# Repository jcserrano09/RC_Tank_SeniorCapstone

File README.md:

brd, sch, and f3z files are in Submission for Manufacture folder

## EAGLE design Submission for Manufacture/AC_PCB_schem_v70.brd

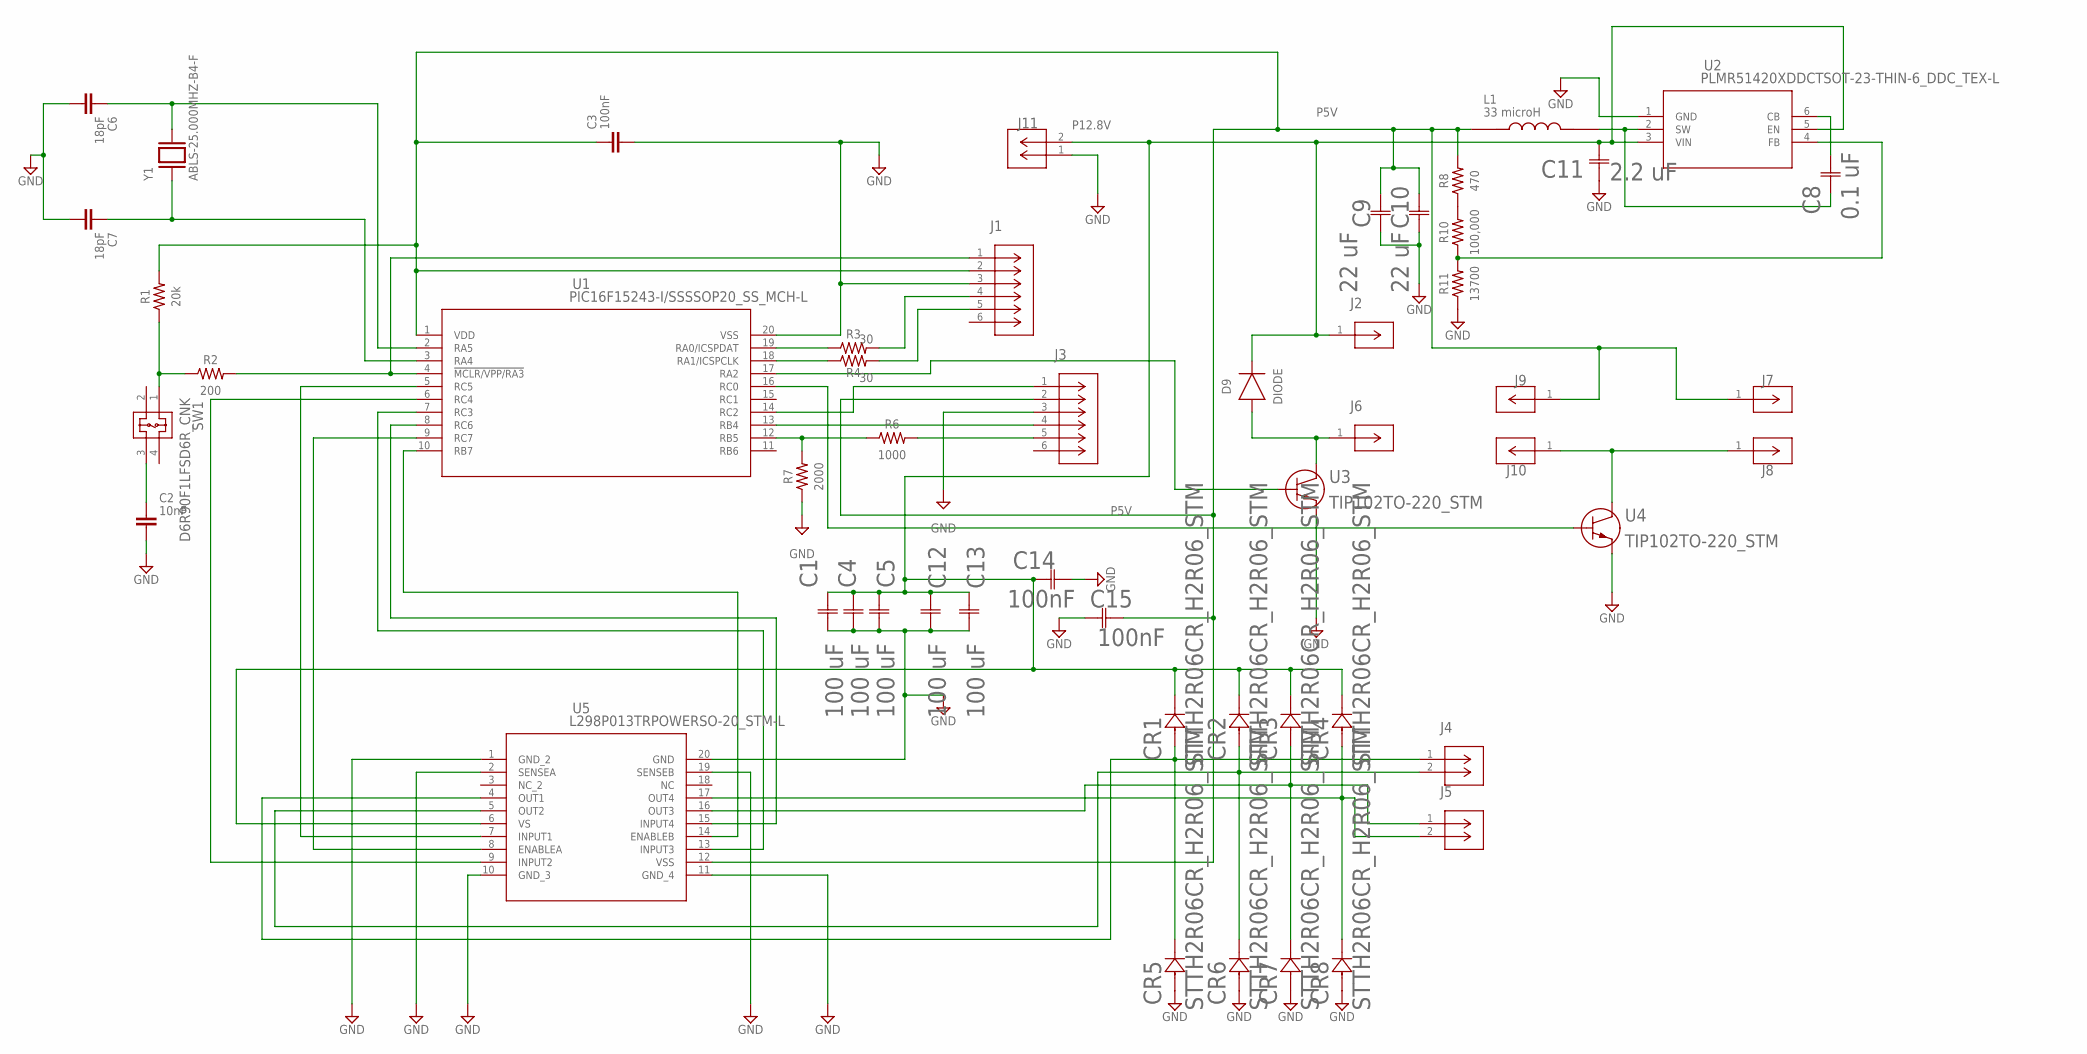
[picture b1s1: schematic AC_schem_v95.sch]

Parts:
C1, C4, C5, C12, C13: 100 uF; CAP_CL31_SAM-L
C2: 10nF; CAPC2012X110
C3: 100nF; CAPC2012X110
C6, C7: 18pF; CAPC2012X110
C8: 0.1 uF; CAP_CL21_SAM-L
C9, C10: 22 uF; CAP_CL21_SAM-L
C11: 2.2 uF; CAP_CL21_SAM-L
C14, C15: 100nF; CAP_CL05_SAM-L
CR1, CR2, CR3, CR4, CR5, CR6, CR7, CR8: STTH2R06CR_H2R06_STM; CR_H2R06_STM
D9: DIODE; DIOM7959X625N
J1: PH1RB-06-UACONN_PH1RB-06; CONN_PH1RB-06
J2, J6, J7, J8, J9, J10: SMC-1-01-1-GTCONN_SMC-1-01-1-GT_ADM; CONN_SMC-1-01-1-GT_ADM
J3: PPTC061LFBN-RCCONN6_061LFBN-RC_SUL; CONN6_061LFBN-RC_SUL
J4, J5, J11: PPTC021LFBN-RCCONN2_LFBN-RC_SUL; CONN2_LFBN-RC_SUL
L1: 33 microH; INDAD1430W80L950D400
R1: 20k; RESC2012X65
R2: 200; RESC2012X65
R3, R4: 30; RESC2012X65
R6: 1000; RESC2012X65
R7: 2000; RESC2012X65
R8: 470; RESC2012X65
R10: 100,000; RESC2012X65
R11: 13700; RESC2012X65
SW1: D6R90F1LFSD6R_CNK; D6R_CNK
U1: PIC16F15243-I/SSSSOP20_SS_MCH-L; SSOP20_SS_MCH-L
U2: PLMR51420XDDCTSOT-23-THIN-6_DDC_TEX-L; SOT-23-THIN-6_DDC_TEX-L
U3, U4: TIP102TO-220_STM; TO-220_STM
U5: L298P013TRPOWERSO-20_STM-L; POWERSO-20_STM-L
Y1: ABLS-25.000MHZ-B4-F; XTAL_ABLS-25.000MHZ-B4-F

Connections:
GND: C1.2, C2.2, C3.2, C4.2, C5.2, C6.2, C7.2, C9.2, C10.2, C11.2, C12.2, C13.2, C14.2, C15.1, CR5.2 (K), CR6.2 (K), CR7.2 (K), CR8.2 (K), J1.3, J3.3, J11.1, R7.1, R11.1, U1.20 (VSS), U2.1 (GND), U3.3 (E), U4.3 (E), U5.1 (GND_2), U5.2 (SENSEA), U5.10 (GND_3), U5.11 (GND_4), U5.19 (SENSEB), U5.20 (GND)
unnamed: J3.5, R6.2
unnamed: J3.4, U1.13 (RB4)
unnamed: J3.1, U1.14 (RC2)
unnamed: U1.5 (RC5), U5.7 (INPUT1)
unnamed: U1.6 (RC4), U5.9 (INPUT2)
unnamed: U1.9 (RC7), U5.8 (ENABLEA)
unnamed: U1.7 (RC3), U5.13 (INPUT3)
unnamed: U1.10 (RB7), U5.14 (ENABLEB)
unnamed: CR2.2 (K), CR6.1 (A), J4.2, U5.5 (OUT2)
unnamed: U1.17 (RA2), U3.1 (B)
unnamed: C2.1, SW1.3
unnamed: CR1.2 (K), CR5.1 (A), J4.1, U5.4 (OUT1)
unnamed: C6.1, U1.2 (RA5), Y1.2
unnamed: CR3.2 (K), CR7.1 (A), J5.1, U5.16 (OUT3)
unnamed: CR4.2 (K), CR8.1 (A), J5.2, U5.17 (OUT4)
unnamed: R10.1, R11.2, U2.4 (FB)
unnamed: R1.1, R2.1, SW1.1
unnamed: J1.1, R2.2, U1.4 (!MCLR/VPP/RA3)
unnamed: J1.4, R3.2
unnamed: J1.5, R4.2
unnamed: R3.1, U1.19 (RA0/ICSPDAT)
unnamed: R4.1, U1.18 (RA1/ICSPCLK)
unnamed: U1.16 (RC0), U4.1 (B)
unnamed: C8.2, U2.6 (CB)
unnamed: C8.1, L1.2, U2.2 (SW)
unnamed: C7.1, U1.3 (RA4), Y1.1
unnamed: D9.2 (A), J6.1, U3.2 (C)
unnamed: R6.1, R7.2, U1.12 (RB5)
unnamed: J8.1, J10.1, U4.2 (C)
unnamed: R8.1, R10.2
unnamed: U1.8 (RC6), U5.15 (INPUT4)
P5V: C3.1, C9.1, C10.1, C15.2, J1.2, J3.2, J7.1, J9.1, L1.1, R1.2, R8.2, U1.1 (VDD), U5.12 (VSS)
P12.8V: C1.1, C4.1, C5.1, C11.1, C12.1, C13.1, C14.1, CR1.1 (A), CR2.1 (A), CR3.1 (A), CR4.1 (A), D9.1 (C), J2.1, J11.2, U2.3 (VIN), U2.5 (EN), U5.6 (VS)

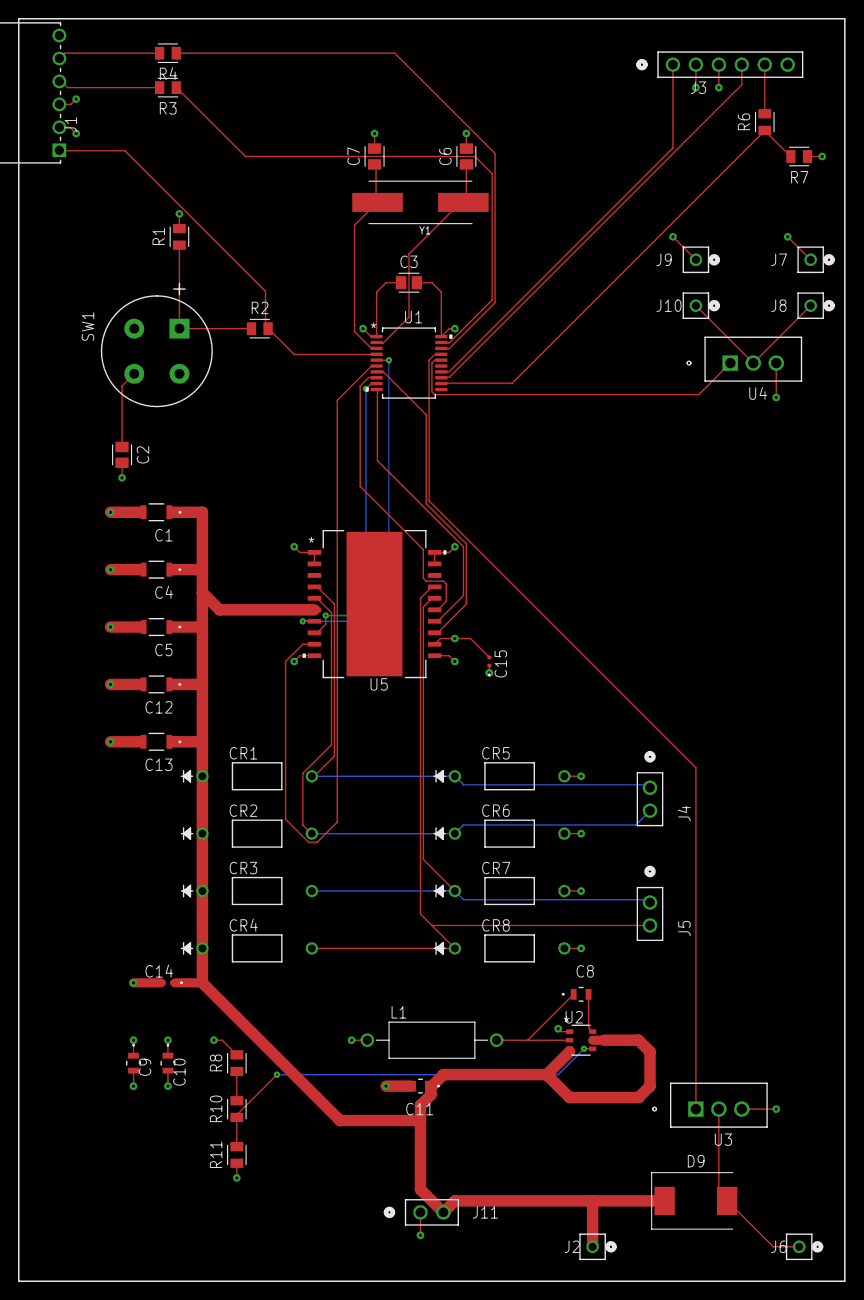
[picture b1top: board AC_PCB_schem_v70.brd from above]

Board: 4 copper layers, 91.4 x 139.7 mm, 52 parts (0 on the bottom side), 34 nets.

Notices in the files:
parts and their libraries:
COPYRIGHT: Copyright (C) 2023 Ultra Librarian. All rights reserved.
